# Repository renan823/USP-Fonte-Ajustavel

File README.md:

# Fonte Ajustável
Alunos: Caio Petroncini, Caroline Akimi e Renan Trofino. 
Este projeto foi construído durante as aulas de eletrônica, e tem como objetivo ser uma **fonte regulável entre 3V e 12V com 100mA.**

## Processos

### Transformador
O transformador é responsável por reduzir a voltagem recebida, tornando-a útil neste dispositivo. Um transformador obedece a seguinte equação:
$$V_{e}.N_{s}=V_{s}.N_{e}$$
A entrada da tomada é de 127V, e a saída do transformador é de aproximadamente 25V.
Então, a razão entre as espiras é:
$${N_{1} \over N_{2}}={V_{max} \over V_{1}}={126,8 \over 25,4}=5$$

### Ponte de diodos
A ponte de diodos é composta por 4 diodos retificadores.
Sua função é tornar a senóide em outra onda, retificando-a.
A corrente alternada é então convertida em corrente contínua.
Para funcionar, os diodos precisam de uma tensão mínima, que, neste modelo,
é de 0.7V cada. Então, a tensão de entrada se torna:
$$V_{2} = 25,4-2.0,7 = 24$$

### Capacitor
O capacitor atua como filtro, eliminando (ou minimizando) o ruído, chamado de ripple.
Considerando um ripple de 10%, temos:
$$R_{eq} = {V_{2} \over I} = {24 \over I} = 216\Omega$$
Onde a corrente I foi obtida usando o simulador Falstad.</br>
A capacitância será dada pela seguinte equação:
$$C = {V_{2} \over ripple.f.R_{eq}.2} = {24 \over 2,4.120.216.2} = 192μF$$

## Componentes usados
Os jumpers (fios) e transformadores foram reaproveitados de outros projetos.
| Qnt. usada | Componente | Valor |
|--------------|------------|-------|
| 04 | Diodo Retificador 1N 4007 (10 unid.) | 2,80 |
| 01 | Capacitor 470μF 63V | 3,46 |
| 01 | Diodo Zener 13V 1/2W (10 unid.) | 7,20 |
| 01 | Resistor 4K7 (50 unid.) | 4,00 |
| 01 | Resistor 680 (50 unid.) | 4,00 |
| 01 | Transistor NPN (5 unid.) | 3,10 |   
| 01 | Potenciômetro linear 10K | 4,50 |
|**Total:** | | **29,00** |

## Circuito no Falstad

Circuito experimental feito no Falstad. Utilizado para os cálculos e prototipação.</br>

## Placa no Eagle

Esquemático feito no Eagle.
</br></br>

Modelo gerado pelo Eagle após criação dos caminhos/rotas de conexão.
</br></br>

## Vídeo explicativo

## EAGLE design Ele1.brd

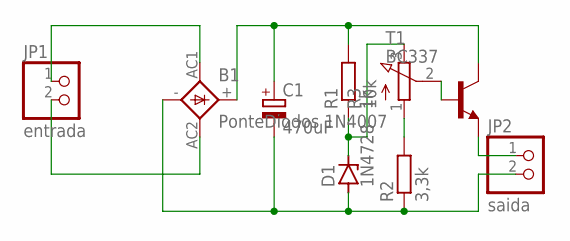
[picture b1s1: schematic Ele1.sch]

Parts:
B1: PonteDiodos 1N4007; 1KAB
C1: 470uF; E5-10,5
D1: 1N4728; DO41Z10
JP1: entrada; 1X02
JP2: saida; 1X02
R1: 1k; 0204/7
R2: 3,3k; 0204/7
R3: 10k; 3RP/1610N
T1: BC337; TO92

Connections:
unnamed: B1.AC1, JP1.1
unnamed: B1.AC2, JP1.2
unnamed: B1.+, C1.+, R1.2, T1.1 (C)
unnamed: JP2.1, T1.3 (E)
unnamed: R2.2, R3.1 (A)
unnamed: B1.-, C1.-, D1.A, JP2.2, R2.1
unnamed: D1.C, R1.1, R3.3 (E)
unnamed: R3.2 (S), T1.2 (B)

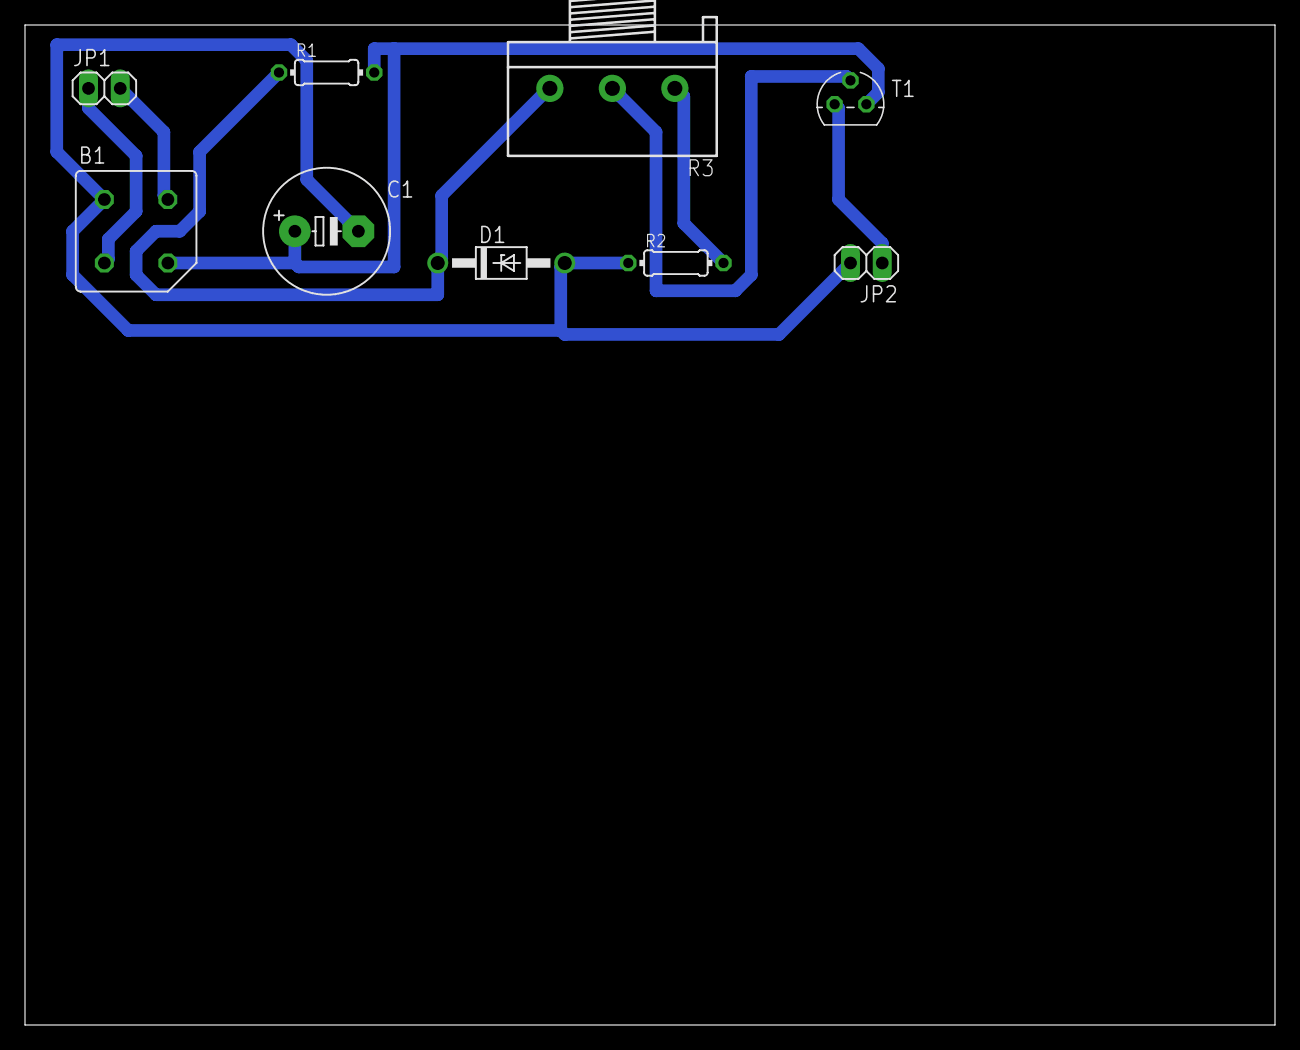
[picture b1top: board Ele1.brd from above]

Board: 2 copper layers, 100.0 x 80.0 mm, 9 parts (0 on the bottom side), 8 nets.

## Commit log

2024-06-18 circuito eagle
